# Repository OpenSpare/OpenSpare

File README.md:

# OpenSpare

**OpenSpare** is an open-source initiative to design and share replacement part for appliances, with the goal of extending their lifespan and reducing our environmental impact.

## 🚀 Why OpenSpare?

Many appliances break down because of simple parts:  
- burnt-out control boards,  
- worn-out mechanical buttons,  
- broken plastic pieces that are no longer available.  

Manufacturers often don’t / no longer provide these parts, or only at a prohibitive cost.  
OpenSpare offers an alternative: a **free library** of designs that anyone can reuse, modify, and manufacture.

We believe that access to open replacement parts is essential to make repair accessible to everyone.  
OpenSpare aims to become a **shared resource** that helps to:  
- extend the life of appliances,  
- reduce electronic waste,
- save money,  
- and strengthen the autonomy of users and repairers.  

## 📦 What’s in this repo?

### Printed Circuits

We provide source files of printed circuits designed with KiCad. Each design will include:

- KiCad source files (project, schematics, board) — freely reusable by anyone.
- Fabrication outputs (Gerber files, NC drill files, Bill of Materials) — ready for manufacturinf by anyone.

Note: Each design will have a documented release status, allowing some designs to be shared even if not yet tested.

### 3D models

[...]

## 🗂️ Repository Structure

- `kicad/` → component libraries (symbols, footprints & 3D models, some datasheets). 
- `parts/` → designs including source files and fabrication files.

## 🤝 Contributing

All contributions are welcome:  
- Adding new parts (PCB, 3D, documentation).  
- Improving existing designs.  
- Manufacturing, testing and sharing feedback. 

👉 A detailed contribution guide is available in the [Wiki](https://github.com/OpenSpare/OpenSpare/wiki).

## License

This project is licensed under the **CERN Open Hardware Licence Version 2 – Weakly Reciprocal (CERN-OHL-W-2.0)**.

You are free to use, study, modify, and manufacture this hardware.  
If you modify the design files themselves, you must release those modifications under the same license.  
However, you are not required to release the source of larger products that merely incorporate this design.

For full details, see the [LICENSE](./LICENSE) file.

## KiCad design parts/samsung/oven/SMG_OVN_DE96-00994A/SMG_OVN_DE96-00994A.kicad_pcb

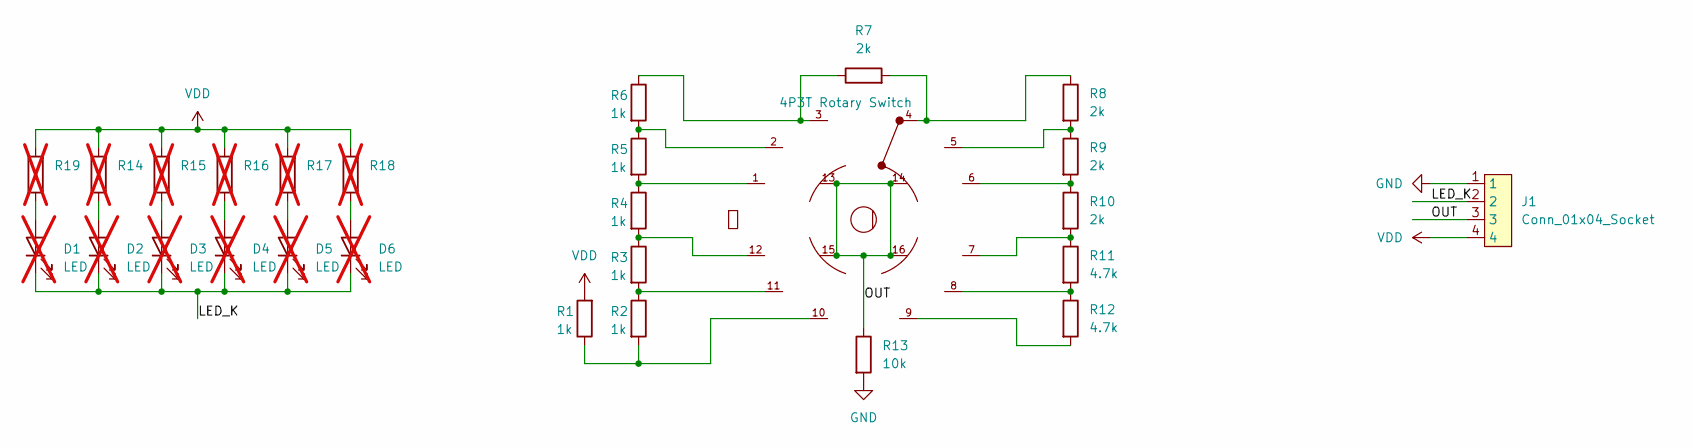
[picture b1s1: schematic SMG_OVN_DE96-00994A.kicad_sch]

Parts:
D1, D2, D3, D4, D5, D6: LED; LED_D3.0mm; not fitted
J1: Conn_01x04_Socket; KON_C2502RD10403T0101PB; Manufacturer1_Part_Numb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 C2502RD10403T0101PB; LCSC Part # C9900221323
R1, R2, R3, R4, R5, R6: 1k; R_0603_1608Metric; Manufacturer1_Part_Numb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 RC0603FR-101KL; LCSC Part # C1512170
R7, R8, R9, R10: 2k; R_0603_1608Metric; Manufacturer1_Part_Numb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 RC0603FR-102KL; LCSC Part # C4103683
R11, R12: 4.7k; R_0603_1608Metric; Manufacturer1_Part_Numb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 RC0603FR-134K7L; LCSC Part # C4269355
R13: 10k; R_0603_1608Metric; Manufacturer1_Part_Numb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 RC0603FR-1010KL; LCSC Part # C4004838
R14, R15, R16, R17, R18, R19: R_0603_1608Metric; not fitted
RS1: 4P3T Rotary Switch; SW_RS240403A0X-HA1-020; Manufacturer2_Part_Numb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 RS240403A0X-HA1-020

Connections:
/LED_K: D1.1 (K), D2.1 (K), D3.1 (K), D4.1 (K), D5.1 (K), D6.1 (K), J1.2
/OUT: J1.3, R13.1, RS1.13, RS1.14, RS1.15, RS1.16
GND: J1.1, R13.2
unnamed: D1.2 (A), R19.1
unnamed: D2.2 (A), R14.1
unnamed: D3.2 (A), R15.1
unnamed: D4.2 (A), R16.1
unnamed: D5.2 (A), R17.1
unnamed: D6.2 (A), R18.1
unnamed: R1.1, R2.2, RS1.10
unnamed: R2.1, R3.2, RS1.11
unnamed: R3.1, R4.2, RS1.12
unnamed: R4.1, R5.2, RS1.1
unnamed: R5.1, R6.2, RS1.2
unnamed: R6.1, R7.1, RS1.3
unnamed: R7.2, R8.1, RS1.4
unnamed: R8.2, R9.1, RS1.5
unnamed: R9.2, R10.1, RS1.6
unnamed: R10.2, R11.1, RS1.7
unnamed: R11.2, R12.1, RS1.8
unnamed: R12.2, RS1.9
VDD: J1.4, R1.2, R14.2, R15.2, R16.2, R17.2, R18.2, R19.2

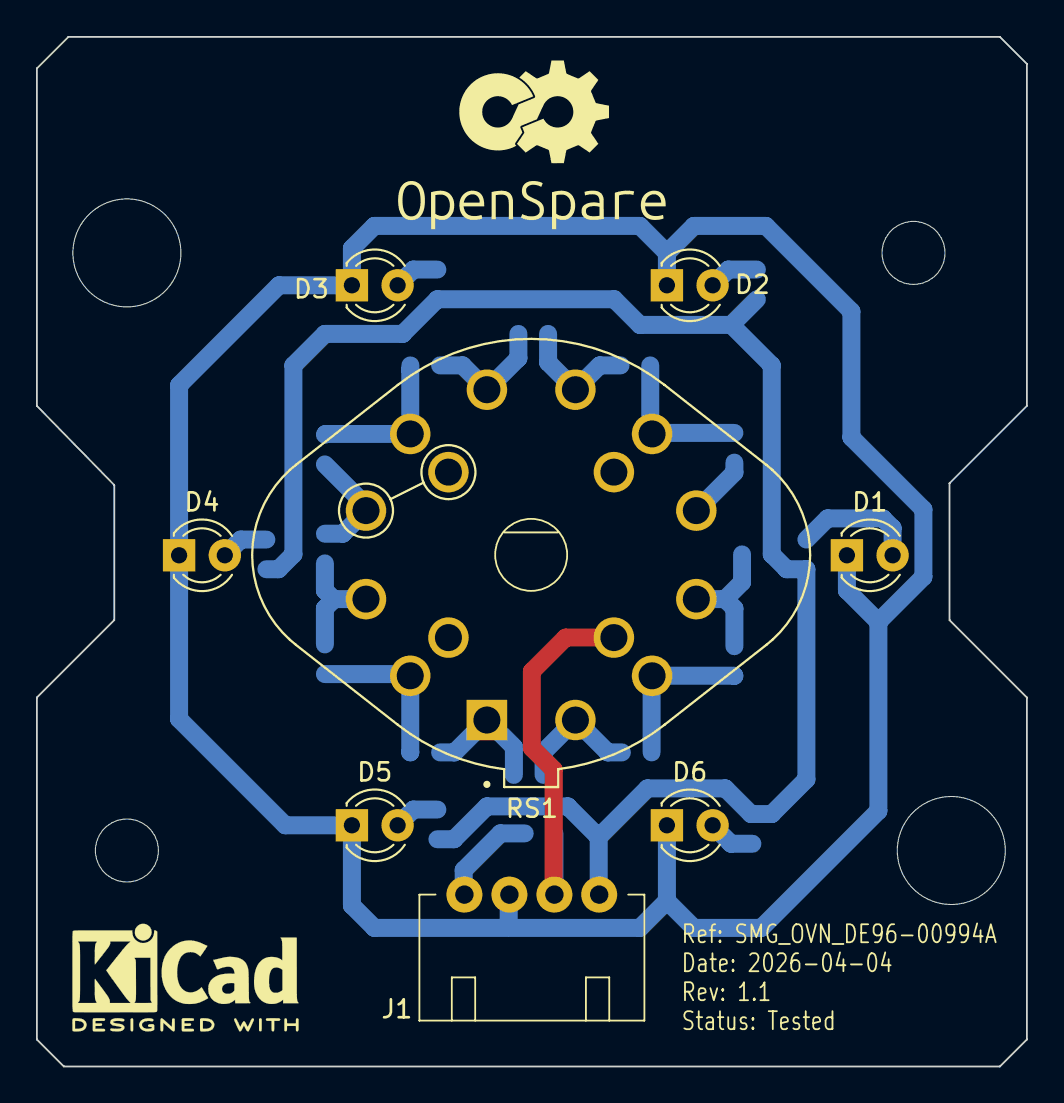
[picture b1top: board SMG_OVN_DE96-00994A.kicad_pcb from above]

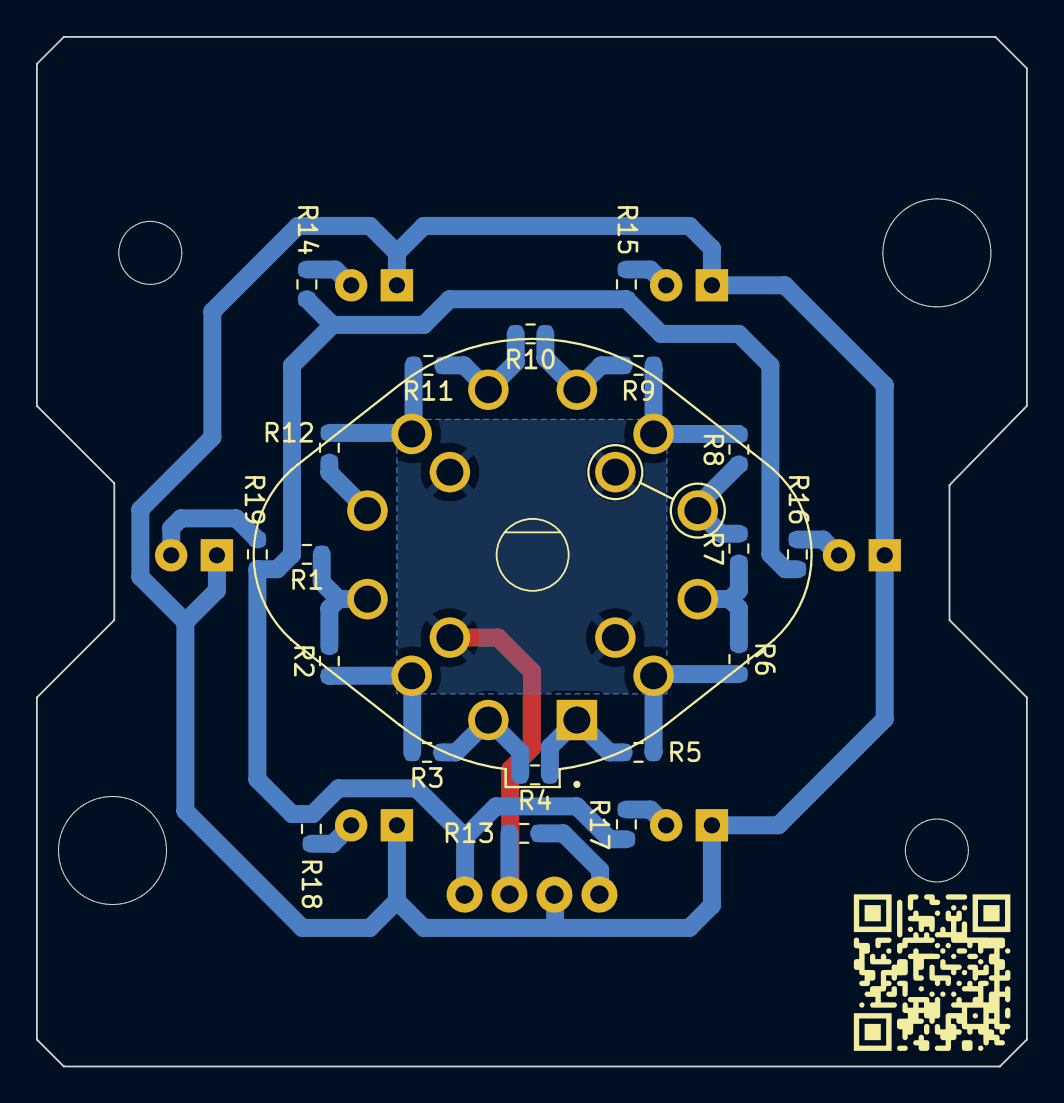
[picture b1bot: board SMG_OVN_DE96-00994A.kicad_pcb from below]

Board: 2 copper layers, 55.0 x 57.2 mm, 27 parts (19 on the bottom side), 22 nets.

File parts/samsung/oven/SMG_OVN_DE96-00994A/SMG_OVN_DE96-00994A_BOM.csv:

"Reference","Qty","Value","DNP","Footprint","Datasheet","Description","Url","Supplier2_Part_Number","Manufacturer2_Name","Manufacturer1_Part_Number","Manufacturer2_Part_Number","Manufacturer1_Name","Supplier1_Name","Supplier1_Part_Number","Supplier2_Name"
"RS1","1","4P3T Rotary Switch","","OpenSpare_footprints:SW_RS240403A0X-HA1-000","kicad-embed://SW_RS240403A0X-HA1-000.pdf","Switch Rotary 4P3T Flatted Shaft 12 positions 30° step","","","ALPS","RS240403A0X-HA1-000","SRRM1C7800","SOUNDWELL  ELECTRONIC","","",""
"R14,R15,R16,R17,R18,R19","6","~","DNP","Resistor_SMD:R_0603_1608Metric","~","Resistor","","","","","","","","",""
"R13","1","10k","","Resistor_SMD:R_0603_1608Metric","~","Thick Film Resistors - SMD General Purpose Chip Resistor 0603, 10kOhms, 5%, 1/10W","","","","RC0603JR-0710KL","","YAGEO","Mouser","603-RC0603JR-0710KL",""
"R11,R12","2","4,7k","","Resistor_SMD:R_0603_1608Metric","~","Thick Film Resistors - SMD General Purpose Chip Resistor 0603, 4.7kOhms, 1%, 1/10W","","","","RC0603FR-134K7L","","YAGEO","Mouser","603-RC0603FR-134K7L",""
"R7,R8,R9,R10","4","2k","","Resistor_SMD:R_0603_1608Metric","~","Thick Film Resistors - SMD General Purpose Chip Resistor 0603, 2kOhms, 1%, 1/10W","","","","RC0603FR-102KL","","YAGEO","Mouser","603-RC0603FR-102KL",""
"R1,R2,R3,R4,R5,R6","6","1k","","Resistor_SMD:R_0603_1608Metric","~","Thick Film Resistors - SMD General Purpose Chip Resistor 0603, 1kOhms, 1%, 1/10W","","","","RC0603FR-101KL ","","YAGEO","Mouser","603-RC0603FR-101KL ",""
"J1","1","Conn_01x04_Socket","","OpenSpare_footprints:KON_C2502RD10403T0101PB","kicad-embed://CON_C2502RDxxx03T0101PB.pdf","2.5 pitch horizontal connector. KR2502 series.","","","YEONHO","C2502RD10403T0101PB","SMAW250-04","KONNRA","","",""
"D1,D2,D3,D4,D5,D6","6","LED","DNP","LED_THT:LED_D3.0mm","~","Light emitting diode","","","","","","","","",""

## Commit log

2025-08-30 Add LICENSE file
    Repo licensed under CERN-OHL-W-2.0
2025-08-30 Add a README.md file
2025-08-31 Add gitignore file
2025-08-31 Ignore *.kicad_prl files
2025-08-31 Initialize OpenSpare's KiCad libs
2025-08-31 WIP on PCB
2025-09-07 Add some minimalist documentation (README)
2025-09-07 Update footprint lib with OpenSpare logos
2025-09-07 Improve OpenSpare symbo lib's default fields
2025-09-07 Add original part pictures
2025-09-07 Minor design modifications
2025-09-08 Create CNAME
2025-09-09 Update README.md to extend project scope
2025-09-10 Update symbol and footprint libs
2025-09-10 Update SMG_OVN_DE96-00994A design (rev 1)
2025-09-10 Generate SMG_OVN_DE96-00994A fab outputs
2025-09-10 Add OpenSpare schematic file template
2025-10-05 Generate output for JLCPCB format
2025-10-05 Add picture of JLCPCB part delivery
2025-10-05 Publish design of SMG_OVN_DE96-00994A rev1
    * Initialize OpenSpare's KiCad libs
    * WIP on PCB
    * Update footprint lib with OpenSpare logos
    * Improve OpenSpare symbo lib's default fields
    * Minor design modifications
    * Add original part pictures
2025-10-19 Add a KiCad project template
2025-10-19 Update README (PCB design contribution)
2026-01-10 Add XL-3030UWC-1W-3V datasheet and 3d model to lib
2026-01-10 Add BSH_FRG_10024820 project (design files)
2026-01-10 Generate BSH_FRG_10024820 production files
2026-01-13 Add Jekyll website structure for GitHub Pages
    - Add _config.yml with Cayman theme
    - Add index.md homepage content
    - Remove duplicate CNAME from root (keep only in /docs)
2026-01-13 Add wiki content to website with navigation
    - Add parts-list.md (parts catalog)
    - Add contributing-pcb.md (PCB design guide)
    - Add navigation bar to all pages
    - Copy wiki images to docs/img/
2026-01-13 Add repository config and Gemfile for local development
    - Add repository setting for GitHub Pages
    - Add Gemfile for local Jekyll preview with Docker
2026-01-13 Add Jekyll generated files to gitignore
2026-01-13 Add visual identity: logo, favicon, and green header
    - Add OpenSpare logo in header
    - Add favicon (small logo)
    - Override Cayman theme with eco-green gradient
2026-01-13 Add interactive parts catalog with card-based filtering
    - Add parts.yml data file with structured catalog (brand/equipment/parts)
    - Add brand logos (Samsung, Bosch) and equipment icons (oven, fridge)
    - Create card-based UI with click navigation between levels
    - Add JavaScript for filtering and back navigation
    - Add expandable compatible devices list (sorted alphabetically)
    - Style cards with hover effects and centered layout
2026-01-14 Add appliance reference search to parts catalog
    - Search input at top of Parts List page
    - Search by appliance model number (min 3 chars)
    - Display matching parts with compatible devices list
    - Limit to 10 matches shown with "(+ X more)" indicator
    - Style compatible devices section with green box in catalog view
2026-01-14 Add homepage before/after comparison slider
    - Interactive slider comparing original vs OpenSpare parts
    - Reorganized homepage with visual comparison as centerpiece
    - Generic drugs analogy messaging
2026-01-14 Refactor parts data structure to decouple parts from brands
    - Separate brands list (with logos) from parts
    - Add equipment_types list (with icons)
    - Parts now flat list with equipment reference
    - Compatible devices reference brand IDs
    - Dynamic filtering: parts shown based on compatible devices
2026-01-14 Improve compatible devices and search matches UI
    - Add scrollable lists for compatible devices and matches
    - Unified yellow style for both sections
    - Matches section now expandable with toggle
    - Display "Matches N device(s)" with arrow indicator
2026-01-14 Add top render and original picture for BSH_FRG_10024820
2026-01-15 Move the contribution guide in github repo
2026-01-15 "Add news page with Jekyll posts and UI improvements
    - Replace Contributing page with News page
    - Add news system using Jekyll posts
    - Create post layout with equipment"
2026-01-16 Adjust mobile navigation button sizes
2026-01-16 Add author information and top render image for SMG_OVN_DE96-00994A
2026-01-16 Add author information and top render image for SMG_OVN_DE96-00994A (#6)
2026-01-16 Add contributor attribution system with AUTHOR.yml
    - Display designer info (avatar, name, tip link) in catalog, news cards and post pages
    - Fetch author data dynamically from GitHub
    - Add side-by-side image comparison in post pages
    - Document AUTHOR.yml format in CONTRIBUTING.md
2026-01-16 Add contact page and form for user feedback
2026-01-22 Add author information and top/bottom images of BSH_FRG_10024820
2026-01-22 Add new brands and logos: Balay, Neff, Siemens, and Constructa
2026-01-22 Add multi-language support (EN/FR)
    - Create /en/ and /fr/ folder structure for content
    - Add root index.html with browser language auto-detection
    - Add language dropdown selector in header navigation
    - Translate all pages: home, parts-list, news, contact
    - Translate all UI strings in JavaScript (catalog, search, BMC button)
    - Add French translations to data files (equipment types, parts)
2026-04-04 Publish design of 10024820 part (BOSCH fridge) rev1
    * Add XL-3030UWC-1W-3V datasheet and 3d model to lib
    * Add BSH_FRG_10024820 project (design files)
    * Generate BSH_FRG_10024820 production files
    * Add top render and original picture for BSH_FRG_10024820
    * Add author information and top/bottom images of BSH_FRG_10024820
2026-04-04 Minor PCB fixes
    - Remove excess of copper near R8
    - Fix placement of RS1 label
2026-04-04 Increase SMG_OVN_DE96-00994A 's revision to 1.1/Tested by fixing component reference for the rotary switch RS1
    - Replace ref RS240403A0X-HA1-000 by the -020 version that has correct output connection specifications
    - Set ALPS SRRM1C7800 as prefered part number for RS1 (the one tested)
    - Improve schematics and pcb to better indicate connection requirements
2026-04-04 Publish 10024820 fridge LED light board on website
    Update parts catalog with full description, images, status and 2314
    compatible models (Bosch, Siemens, Balay, Neff, Constructa).
    Add EN/FR news posts.

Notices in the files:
parts/samsung/oven/SMG_OVN_DE96-00994A/SMG_OVN_DE96-00994A.kicad_pcb:
SPDX-License-Identifier: CERN-OHL-W-2.0
© 2025 OpenSpare contributors
